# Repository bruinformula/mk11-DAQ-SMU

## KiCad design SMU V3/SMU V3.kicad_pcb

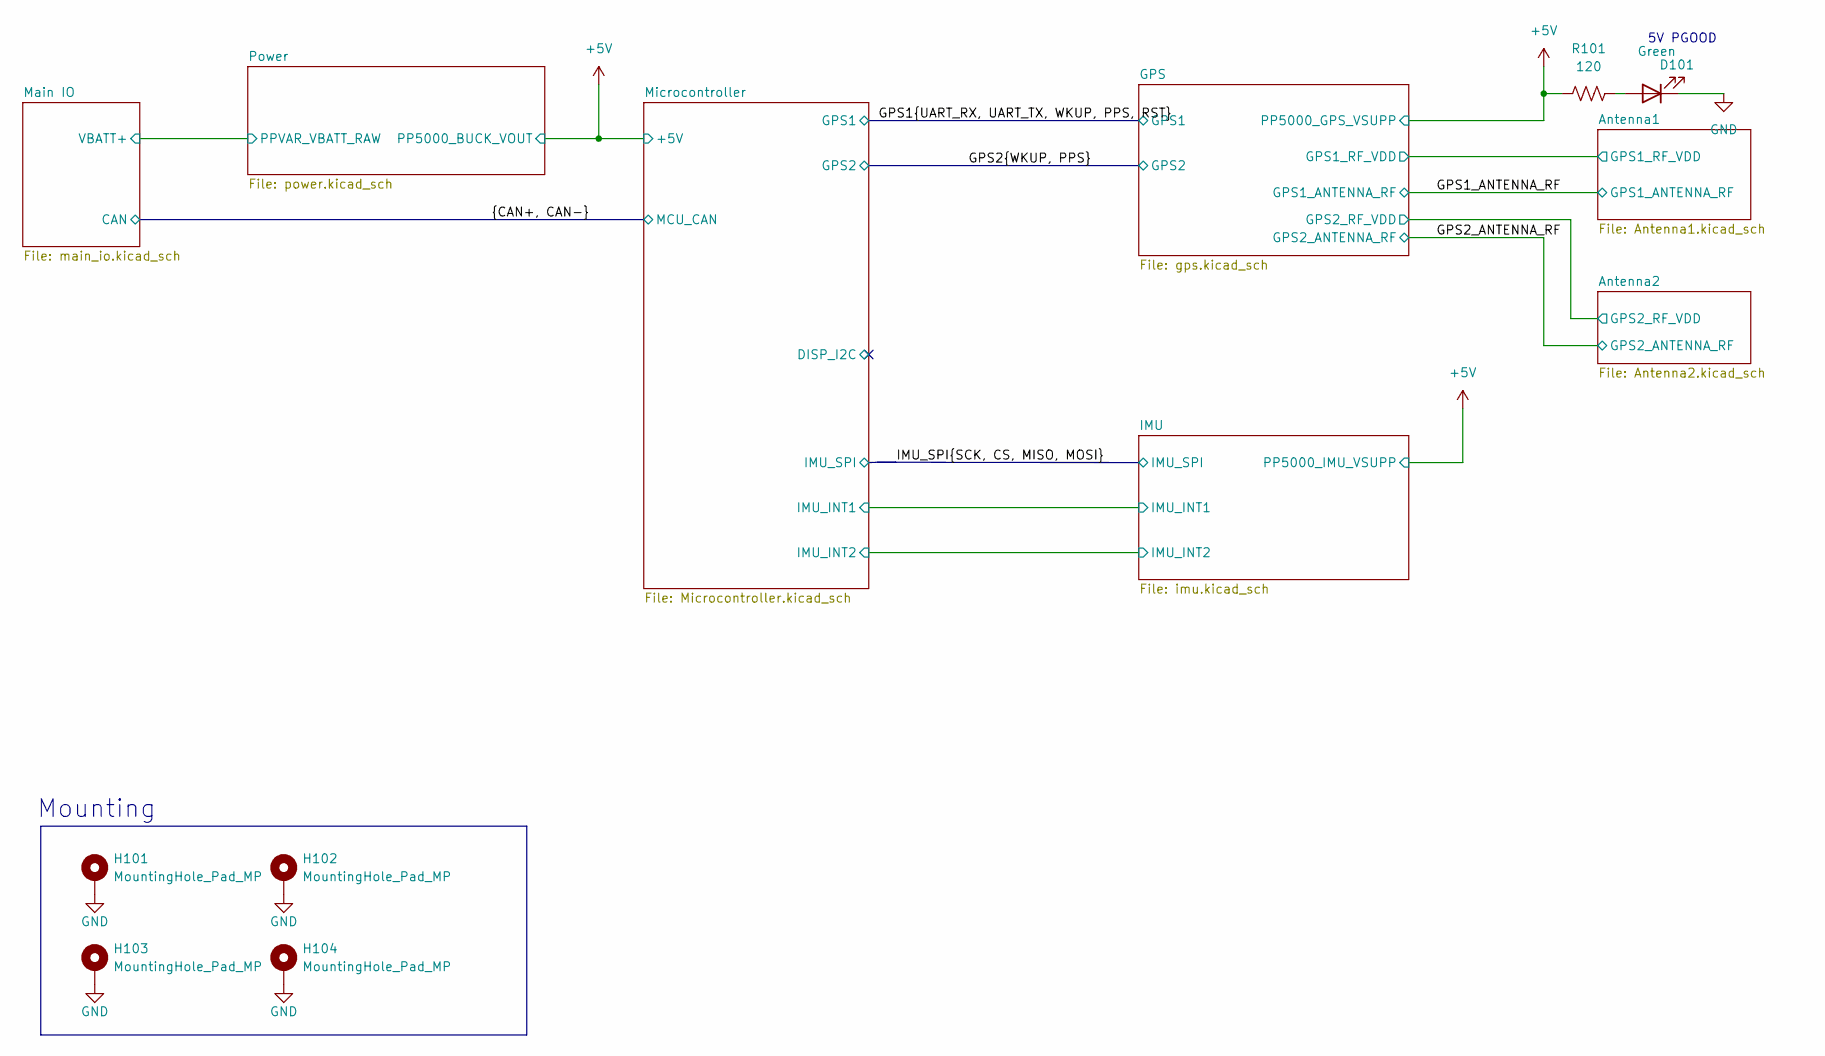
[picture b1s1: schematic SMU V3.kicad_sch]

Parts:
D101: Green; D_0805_2012Metric_Pad1.15x1.40mm_HandSolder; Mouser P/N 755-SMLMN2ECTT86C; Digikey P/N 846-SMLMN2ECTT86CCT-ND
H101, H102, H103, H104: MountingHole_Pad_MP; MountingHole_2.7mm_M2.5_Pad_Via; Mouser P/N N/A; Digikey P/N N/A
R101: 120; R_0603_1608Metric_Pad0.98x0.95mm_HandSolder; Mouser P/N 708-RMCF0603FT120R; Digikey P/N RMCF0603FT120RCT-ND

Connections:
+5V: R101.1; also elsewhere on the board
GND: D101.1 (K), H101.1 (1_1), H102.1 (1_1), H103.1 (1_1), H104.1 (1_1); also elsewhere on the board
unnamed: D101.2 (A), R101.2

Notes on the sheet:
5V PGOOD
Mounting

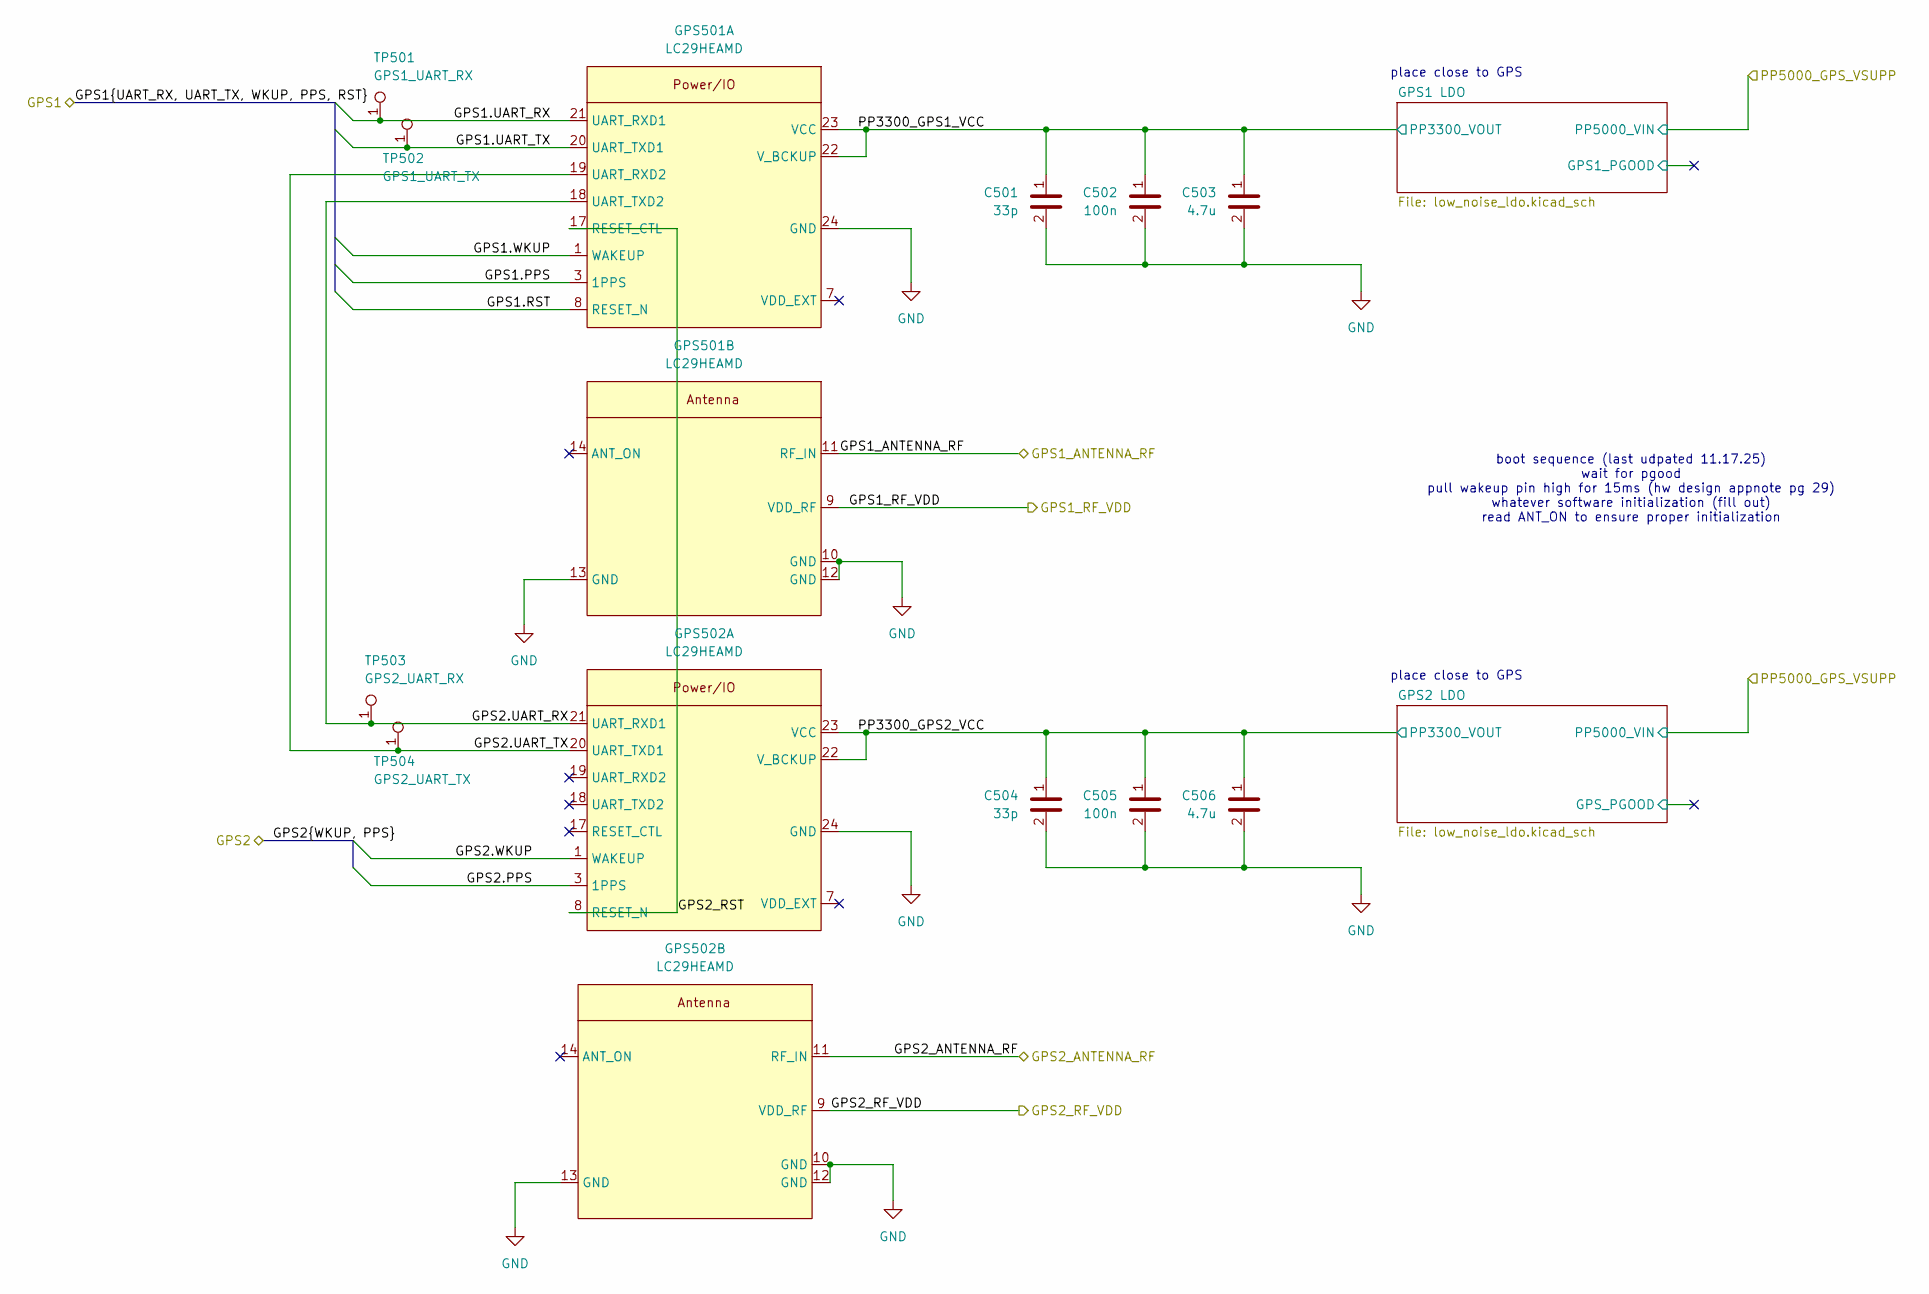
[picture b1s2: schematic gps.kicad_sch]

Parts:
C501, C504: 33p; C_0402_1005Metric_Pad0.74x0.62mm_HandSolder; LCSC P/N C1562
C502, C505: 100n; C_0402_1005Metric_Pad0.74x0.62mm_HandSolder; LCSC P/N C1525
C503, C506: 4.7u; C_0603_1608Metric_Pad1.08x0.95mm_HandSolder; LCSC P/N C19666
GPS501, GPS502: LC29HEAMD; Quectel LC49
TP501: GPS1_UART_RX; TestPoint_Keystone_5019_Miniature; Manufacturer P/N RH-5019; Digikey P/N 36-5019CT-ND
TP502: GPS1_UART_TX; TestPoint_Keystone_5019_Miniature; Manufacturer P/N RH-5019; Digikey P/N 36-5019CT-ND
TP503: GPS2_UART_RX; TestPoint_Keystone_5019_Miniature; Manufacturer P/N RH-5019; Digikey P/N 36-5019CT-ND
TP504: GPS2_UART_TX; TestPoint_Keystone_5019_Miniature; Manufacturer P/N RH-5019; Digikey P/N 36-5019CT-ND

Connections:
/Antenna1/GPS1_RF_VDD: GPS501.9 (VDD_RF); also elsewhere on the board
/Antenna2/GPS2_RF_VDD: GPS502.9 (VDD_RF); also elsewhere on the board
/GPS1.PPS: GPS501.3 (1PPS); also elsewhere on the board
/GPS1.RST: GPS501.8 (RESET_N); also elsewhere on the board
/GPS1.UART_RX: GPS501.21 (UART_RXD1), TP501.1; also elsewhere on the board
/GPS1.UART_TX: GPS501.20 (UART_TXD1), TP502.1; also elsewhere on the board
/GPS1.WKUP: GPS501.1 (WAKEUP); also elsewhere on the board
/GPS1_ANTENNA_RF: GPS501.11 (RF_IN); also elsewhere on the board
/GPS2.PPS: GPS502.3 (1PPS); also elsewhere on the board
/GPS2.WKUP: GPS502.1 (WAKEUP); also elsewhere on the board
/GPS2_ANTENNA_RF: GPS502.11 (RF_IN); also elsewhere on the board
/GPS/GPS2.UART_RX: GPS501.18 (UART_TXD2), GPS502.21 (UART_RXD1), TP503.1
/GPS/GPS2.UART_TX: GPS501.19 (UART_RXD2), GPS502.20 (UART_TXD1), TP504.1
/GPS/GPS2_RST: GPS501.17 (RESET_CTL), GPS502.8 (RESET_N)
/GPS/PP3300_GPS1_VCC: C501.1, C502.1, C503.1, GPS501.22 (V_BCKUP), GPS501.23 (VCC); also elsewhere on the board
/GPS/PP3300_GPS2_VCC: C504.1, C505.1, C506.1, GPS502.22 (V_BCKUP), GPS502.23 (VCC); also elsewhere on the board
GND: C501.2, C502.2, C503.2, C504.2, C505.2, C506.2, GPS501.10 (GND), GPS501.12 (GND), GPS501.13 (GND), GPS501.24 (GND), GPS502.10 (GND), GPS502.12 (GND), GPS502.13 (GND), GPS502.24 (GND); also elsewhere on the board

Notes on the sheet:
boot sequence (last udpated 11.17.25) wait for pgood pull wakeup pin high for 15ms (hw design appnote pg 29) whatever software initialization (fill out) read ANT_ON to ensure proper initialization
place close to GPS

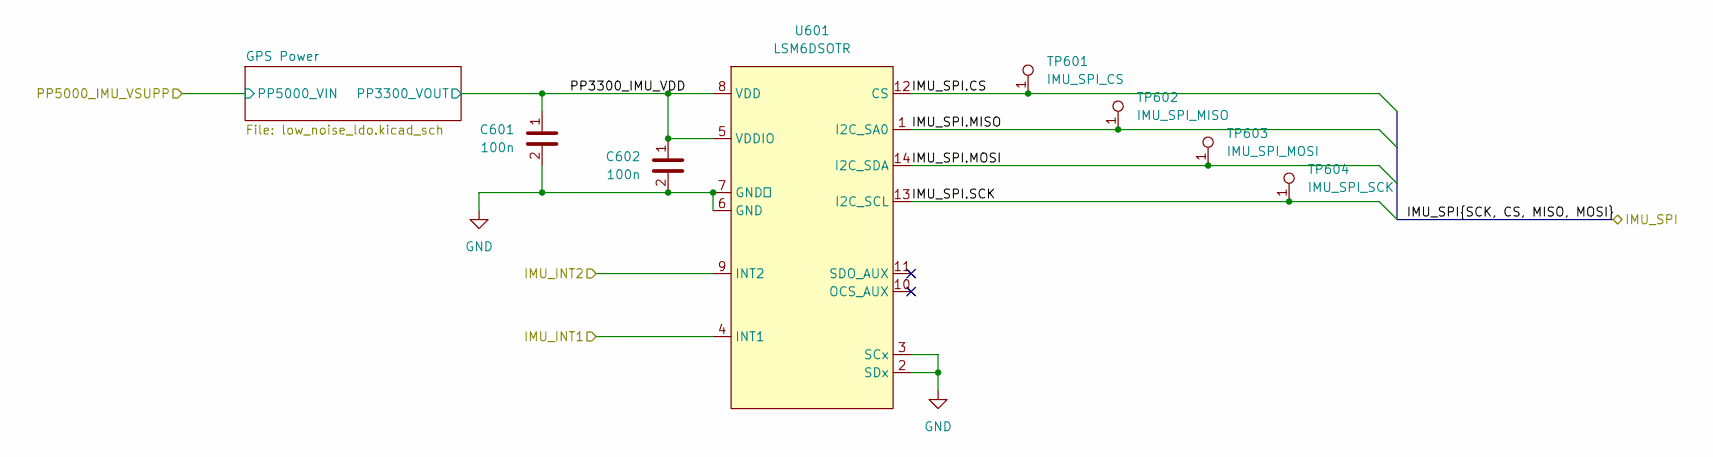
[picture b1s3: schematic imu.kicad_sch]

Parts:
C601, C602: 100n; C_0402_1005Metric_Pad0.74x0.62mm_HandSolder; LCSC P/N C1525
TP601: IMU_SPI_CS; TestPoint_Keystone_5019_Miniature; Manufacturer P/N RH-5019; Digikey P/N 36-5019CT-ND
TP602: IMU_SPI_MISO; TestPoint_Keystone_5019_Miniature; Manufacturer P/N RH-5019; Digikey P/N 36-5019CT-ND
TP603: IMU_SPI_MOSI; TestPoint_Keystone_5019_Miniature; Manufacturer P/N RH-5019; Digikey P/N 36-5019CT-ND
TP604: IMU_SPI_SCK; TestPoint_Keystone_5019_Miniature; Manufacturer P/N RH-5019; Digikey P/N 36-5019CT-ND
U601: LSM6DSOTR; LGA-14_3x2.5mm_P0.5mm_LayoutBorder3x4y; Manufacturer P/N LSM6DSOTR; Digikey P/N 497-18181-2-ND

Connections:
/IMU/IMU_INT1: U601.4 (INT1); also elsewhere on the board
/IMU/IMU_INT2: U601.9 (INT2); also elsewhere on the board
/IMU/PP3300_IMU_VDD: C601.1, C602.1, U601.5 (VDDIO), U601.8 (VDD); also elsewhere on the board
/IMU_SPI.CS: TP601.1, U601.12 (CS); also elsewhere on the board
/IMU_SPI.MISO: TP602.1, U601.1 (I2C_SA0); also elsewhere on the board
/IMU_SPI.MOSI: TP603.1, U601.14 (I2C_SDA); also elsewhere on the board
/IMU_SPI.SCK: TP604.1, U601.13 (I2C_SCL); also elsewhere on the board
GND: C601.2, C602.2, U601.2 (SDx), U601.3 (SCx), U601.6 (GND), U601.7 (GND); also elsewhere on the board

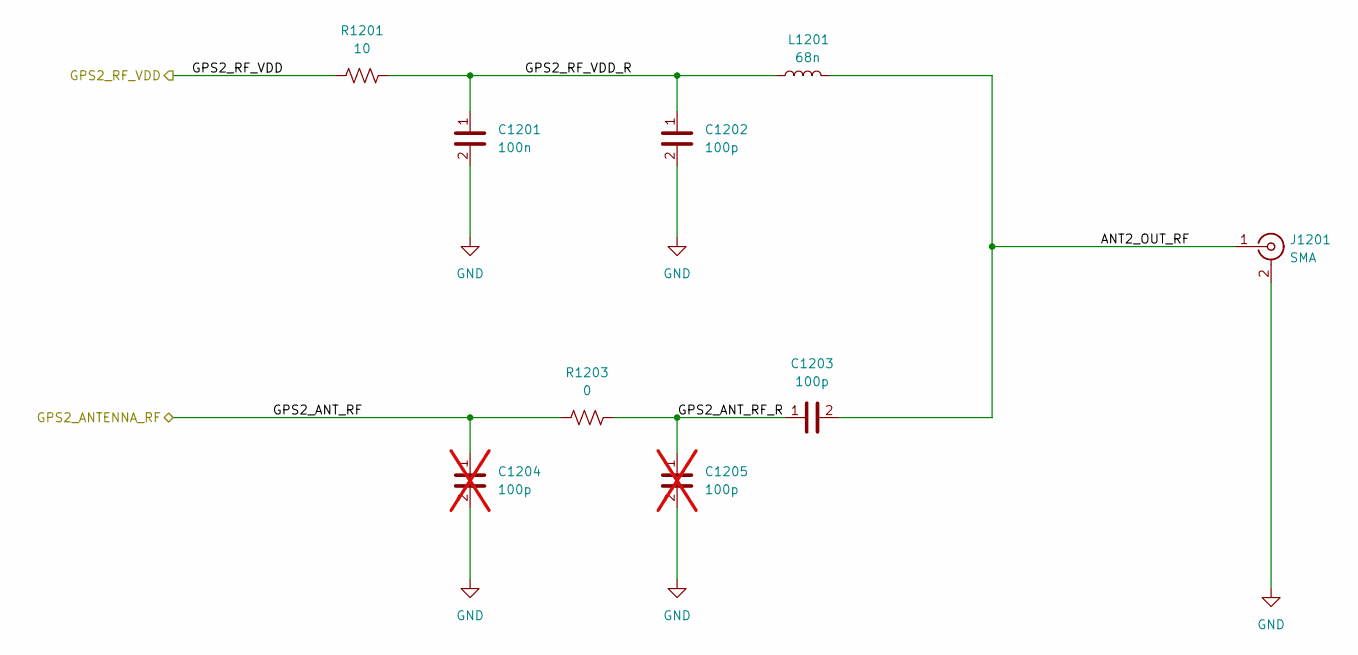
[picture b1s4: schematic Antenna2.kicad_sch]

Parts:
C1201: 100n; C_0402_1005Metric_Pad0.74x0.62mm_HandSolder; Manufacturer P/N CL05B104KB54PNC; LCSC P/N C307331
C1202, C1203: 100p; C_0402_1005Metric_Pad0.74x0.62mm_HandSolder; LCSC P/N C1546
C1204, C1205: 100p; C_0402_1005Metric_Pad0.74x0.62mm_HandSolder; LCSC P/N C1546; not fitted
J1201: SMA; THT SMA; Manufacturer P/N SMA-J-P-H-ST-TH1; Digikey P/N SAM8971-ND
L1201: 68n; L_0402_1005Metric_Pad0.77x0.64mm_HandSolder; Manufacturer P/N LQW15AN68NG0ZD; Digikey P/N 490-17700-2-ND
R1201: 10; R_0402_1005Metric_Pad0.72x0.64mm_HandSolder; Mouser P/N 708-RMCF0402FT10R0; Digikey P/N RMCF0402FT10R0CT-ND
R1203: 0; R_0402_1005Metric_Pad0.72x0.64mm_HandSolder; Mouser P/N 708-RMCF0402ZT0R00; Digikey P/N RMCF0402ZT0R00CT-ND

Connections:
/Antenna2/ANT2_OUT_RF: C1203.2, J1201.1, L1201.1
/Antenna2/GPS2_ANT_RF_R: C1203.1, C1205.1, R1203.2
/Antenna2/GPS2_RF_VDD: R1201.1; also elsewhere on the board
/Antenna2/GPS2_RF_VDD_R: C1201.1, C1202.1, L1201.2, R1201.2
/GPS2_ANTENNA_RF: C1204.1, R1203.1; also elsewhere on the board
GND: C1201.2, C1202.2, C1204.2, C1205.2, J1201.2; also elsewhere on the board

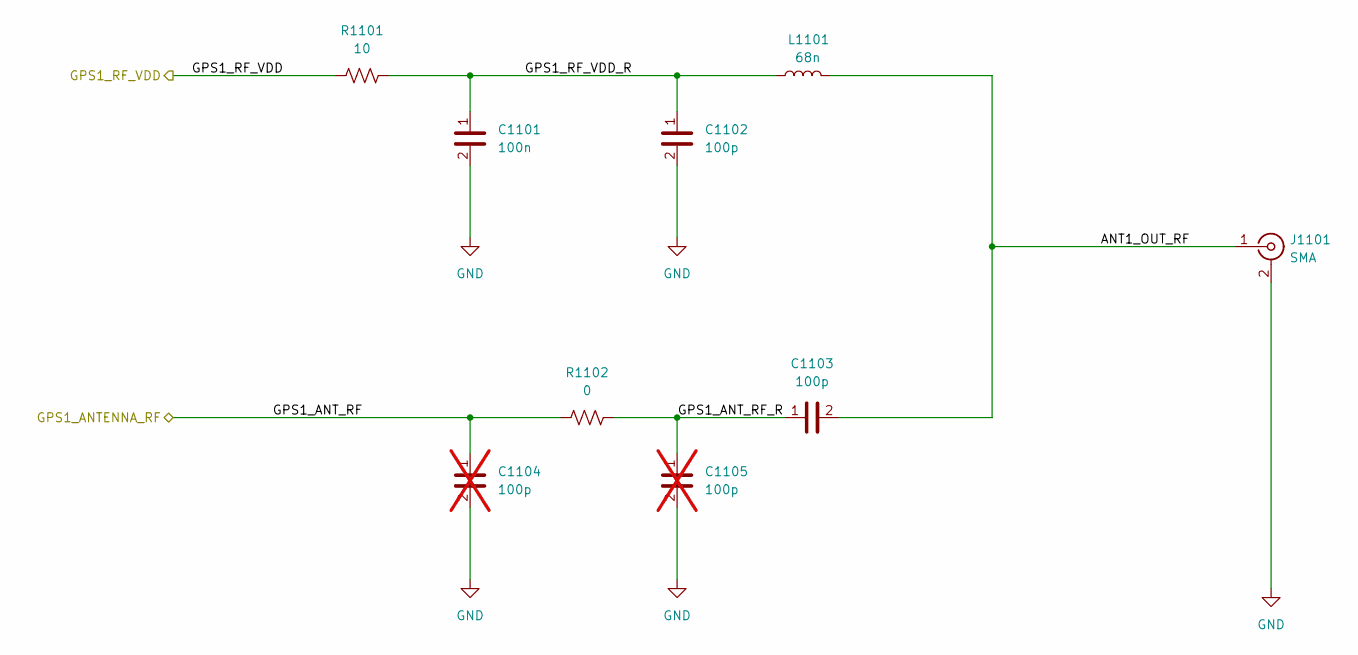
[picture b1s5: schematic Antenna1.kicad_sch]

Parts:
C1101: 100n; C_0402_1005Metric_Pad0.74x0.62mm_HandSolder; Manufacturer P/N CL05B104KB54PNC; LCSC P/N C307331
C1102, C1103: 100p; C_0402_1005Metric_Pad0.74x0.62mm_HandSolder; LCSC P/N C1546
C1104, C1105: 100p; C_0402_1005Metric_Pad0.74x0.62mm_HandSolder; LCSC P/N C1546; not fitted
J1101: SMA; THT SMA; Manufacturer P/N SMA-J-P-H-ST-TH1; Digikey P/N SAM8971-ND
L1101: 68n; L_0402_1005Metric_Pad0.77x0.64mm_HandSolder; Manufacturer P/N LQW15AN68NG0ZD; Digikey P/N 490-17700-2-ND
R1101: 10; R_0402_1005Metric_Pad0.72x0.64mm_HandSolder; Mouser P/N 708-RMCF0402FT10R0; Digikey P/N RMCF0402FT10R0CT-ND
R1102: 0; R_0402_1005Metric_Pad0.72x0.64mm_HandSolder; Mouser P/N 708-RMCF0402ZT0R00; Digikey P/N RMCF0402ZT0R00CT-ND

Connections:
/Antenna1/ANT1_OUT_RF: C1103.2, J1101.1, L1101.1
/Antenna1/GPS1_ANT_RF_R: C1103.1, C1105.1, R1102.2
/Antenna1/GPS1_RF_VDD: R1101.1; also elsewhere on the board
/Antenna1/GPS1_RF_VDD_R: C1101.1, C1102.1, L1101.2, R1101.2
/GPS1_ANTENNA_RF: C1104.1, R1102.1; also elsewhere on the board
GND: C1101.2, C1102.2, C1104.2, C1105.2, J1101.2; also elsewhere on the board

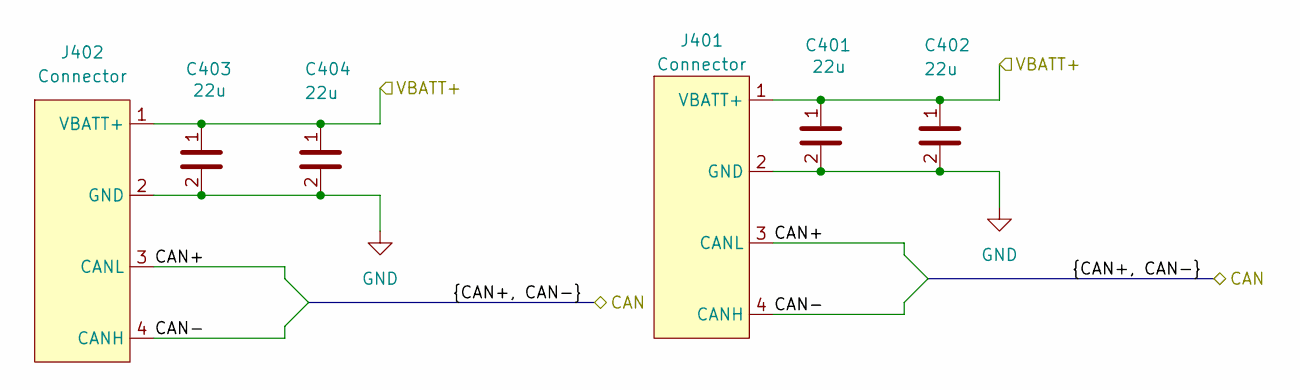
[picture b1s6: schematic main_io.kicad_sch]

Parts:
C401, C402, C403, C404: 22u; C_0805_2012Metric_Pad1.18x1.45mm_HandSolder; Mouser P/N 187-CL21A226MAYNNNE
J401, J402: Connector; Molex_Micro-Fit_3.0_43650-0400_1x04_P3.00mm_Horizontal; Manufacturer P/N 0436500401; Digikey P/N WM1867-ND

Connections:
/CAN+: J401.3 (CANL), J402.3 (CANL); also elsewhere on the board
/CAN-: J401.4 (CANH), J402.4 (CANH); also elsewhere on the board
/Main IO/VBATT+: C401.1, C402.1, C403.1, C404.1, J401.1 (VBATT+), J402.1 (VBATT+); also elsewhere on the board
GND: C401.2, C402.2, C403.2, C404.2, J401.2 (GND), J402.2 (GND); also elsewhere on the board

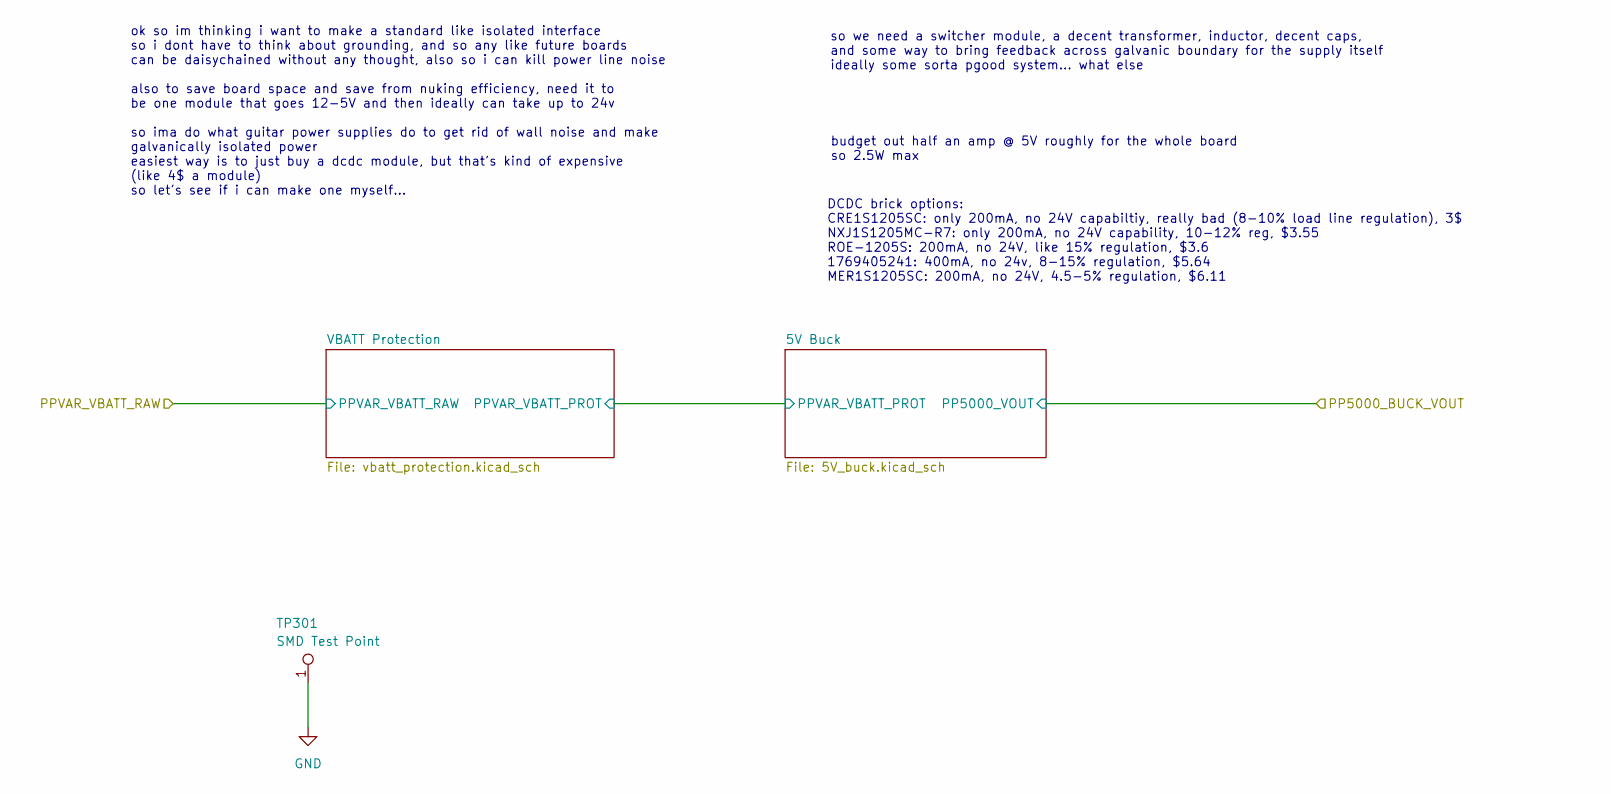
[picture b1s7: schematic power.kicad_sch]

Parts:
TP301: SMD Test Point; TestPoint_Keystone_5019_Miniature; Manufacturer P/N RH-5019; Digikey P/N 36-5019CT-ND

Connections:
GND: TP301.1; also elsewhere on the board

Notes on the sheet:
ok so im thinking i want to make a standard like isolated interface so i dont have to think about grounding, and so any like future boards can be daisychained without any thought, also so i can kill power line noise also to save board space and save from nuking efficiency, need it to be one module 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
so we need a switcher module, a decent transformer, inductor, decent caps, and some way to bring feedback across galvanic boundary for the supply itself ideally some sorta pgood system... what else
DCDC brick options: CRE1S1205SC: only 200mA, no 24V capabiltiy, really bad (8-10% load line regulation), 3$ NXJ1S1205MC-R7: only 200mA, no 24V capability, 10-12% reg, $3.55 ROE-1205S: 200mA, no 24V, like 15% regulation, $3.6 1769405241: 400mA, no 24v, 8-15% regulation, $5.64 MER1S1205SC: 200mA, no 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
budget out half an amp @ 5V roughly for the whole board so 2.5W max

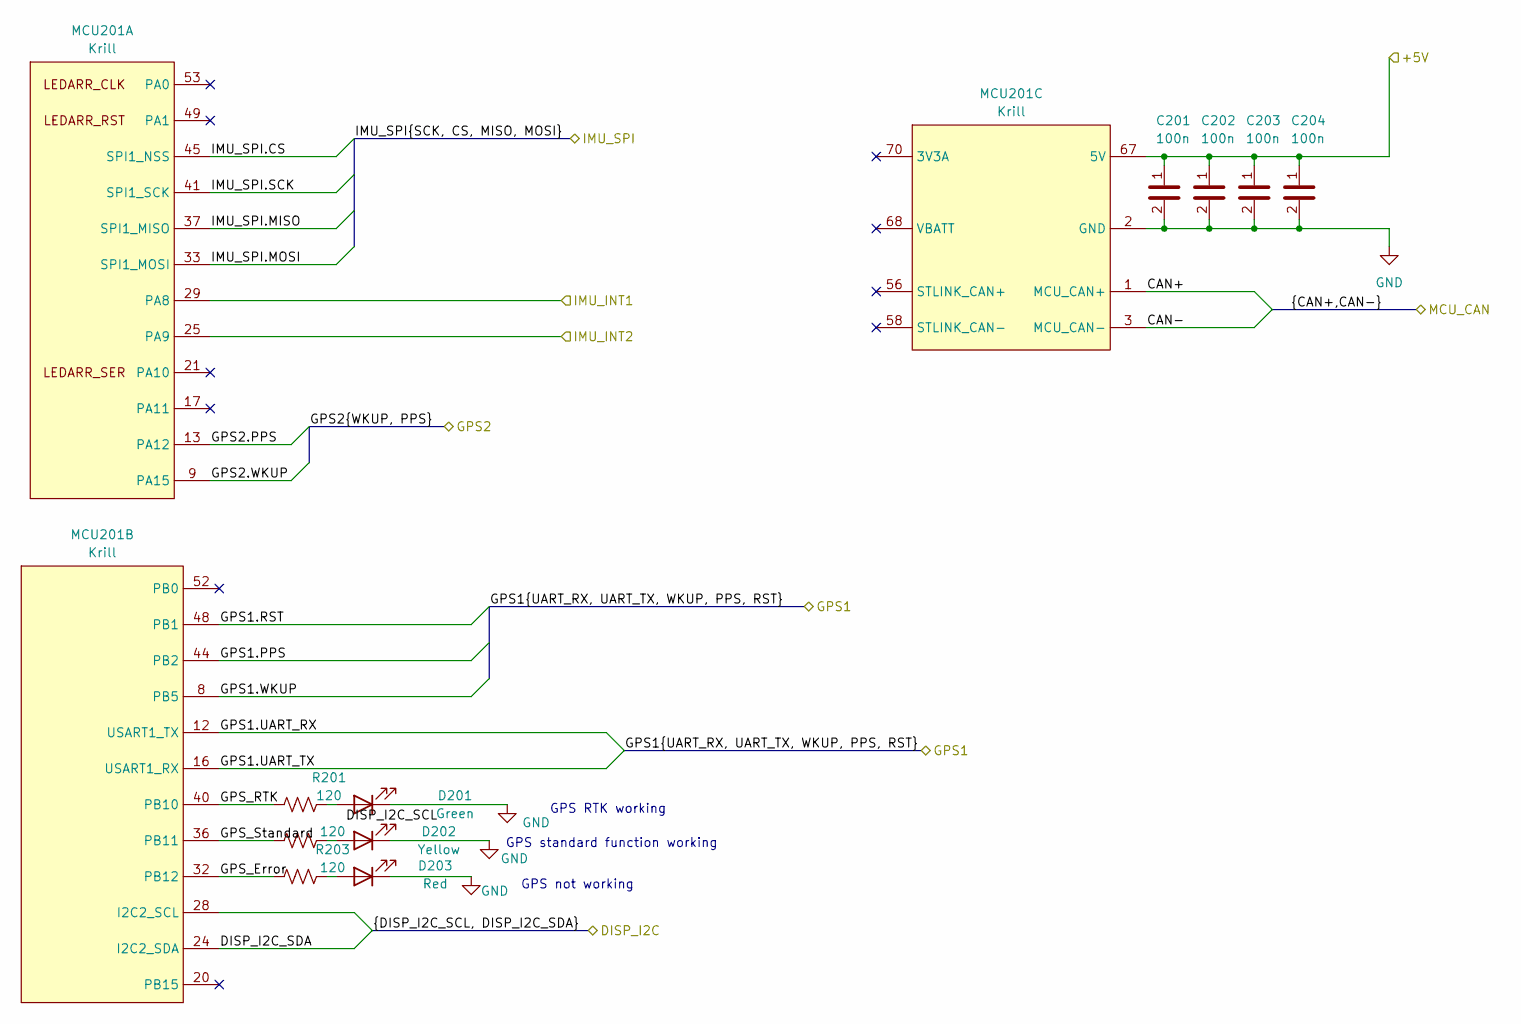
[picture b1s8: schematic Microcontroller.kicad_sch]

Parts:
C201, C202, C203, C204: 100n; C_0402_1005Metric_Pad0.74x0.62mm_HandSolder; LCSC P/N C1525
D201: Green; D_0805_2012Metric_Pad1.15x1.40mm_HandSolder; Mouser P/N 755-SMLMN2ECTT86C; Digikey P/N 846-SMLMN2ECTT86CCT-ND
D202: Yellow; D_0805_2012Metric_Pad1.15x1.40mm_HandSolder; Mouser P/N 645-599-0140-007F; Digikey P/N 350-4356-1-ND
D203: Red; D_0603_1608Metric_Pad1.05x0.95mm_HandSolder; Mouser P/N 720-LRQ976.01; Digikey P/N 475-LRQ976.01-P2R2-1CT-ND
MCU201: Krill; Manufacturer P/N 2E0BC21-S85BM-7H; Digikey P/N 609-MDT850M01501CT-ND
R201, R202, R203: 120; R_0603_1608Metric_Pad0.98x0.95mm_HandSolder; Mouser P/N 708-RMCF0603FT120R; Digikey P/N RMCF0603FT120RCT-ND

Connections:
+5V: C201.1, C202.1, C203.1, C204.1, MCU201.67 (5V), MCU201.69 (5V), MCU201.71 (5V); also elsewhere on the board
/CAN+: MCU201.1 (MCU_CAN+); also elsewhere on the board
/CAN-: MCU201.3 (MCU_CAN-); also elsewhere on the board
/GPS1.PPS: MCU201.44 (PB2); also elsewhere on the board
/GPS1.RST: MCU201.48 (PB1); also elsewhere on the board
/GPS1.UART_RX: MCU201.12 (USART1_TX); also elsewhere on the board
/GPS1.UART_TX: MCU201.16 (USART1_RX); also elsewhere on the board
/GPS1.WKUP: MCU201.8 (PB5); also elsewhere on the board
/GPS2.PPS: MCU201.13 (PA12); also elsewhere on the board
/GPS2.WKUP: MCU201.9 (PA15); also elsewhere on the board
/IMU/IMU_INT1: MCU201.29 (PA8); also elsewhere on the board
/IMU/IMU_INT2: MCU201.25 (PA9); also elsewhere on the board
/IMU_SPI.CS: MCU201.45 (SPI1_NSS); also elsewhere on the board
/IMU_SPI.MISO: MCU201.37 (SPI1_MISO); also elsewhere on the board
/IMU_SPI.MOSI: MCU201.33 (SPI1_MOSI); also elsewhere on the board
/IMU_SPI.SCK: MCU201.41 (SPI1_SCK); also elsewhere on the board
/Microcontroller/DISP_I2C_SDA: MCU201.24 (I2C2_SDA)
/Microcontroller/GPS_Error: MCU201.32 (PB12), R203.1
/Microcontroller/GPS_RTK: MCU201.40 (PB10), R201.1
/Microcontroller/GPS_Standard: MCU201.36 (PB11), R202.1
GND: C201.2, C202.2, C203.2, C204.2, D201.1 (K), D202.1 (K), D203.1 (K), MCU201.2 (GND), MCU201.4 (GND), MCU201.5 (GND), MCU201.6 (GND), MCU201.7 (GND), MCU201.10 (GND), MCU201.11 (GND), MCU201.14 (GND), MCU201.15 (GND), MCU201.18 (GND), MCU201.19 (GND), MCU201.22 (GND), MCU201.23 (GND), MCU201.26 (GND), MCU201.27 (GND), MCU201.30 (GND), MCU201.31 (GND), MCU201.34 (GND), MCU201.35 (GND), MCU201.38 (GND), MCU201.39 (GND), MCU201.42 (GND), MCU201.43 (GND), MCU201.46 (GND), MCU201.47 (GND), MCU201.50 (GND), MCU201.51 (GND), MCU201.54 (GND), MCU201.55 (GND), MCU201.57 (GND), MCU201.73 (GND), MCU201.75 (GND); also elsewhere on the board
unnamed: D201.2 (A), R201.2
unnamed: D202.2 (A), R202.2
unnamed: D203.2 (A), R203.2

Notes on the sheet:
GPS standard function working
GPS not working
GPS RTK working

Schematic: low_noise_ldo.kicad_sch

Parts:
C701, C702: 2.2u; C_0402_1005Metric_Pad0.74x0.62mm_HandSolder; LCSC P/N C12530
D701: Green; D_0805_2012Metric_Pad1.15x1.40mm_HandSolder; Mouser P/N 755-SMLMN2ECTT86C; Digikey P/N 846-SMLMN2ECTT86CCT-ND
R701: 120; R_0603_1608Metric_Pad0.98x0.95mm_HandSolder; Mouser P/N 708-RMCF0603FT120R; Digikey P/N RMCF0603FT120RCT-ND
U701: TPS7A2033PDBVR; SOT-23-5_HandSoldering; Manufacturer P/N TPS7A2033PDBVR; Digikey P/N 296-TPS7A2033PDBVRCT-ND

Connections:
+5V: C701.1, U701.1 (VIN), U701.3 (EN); also elsewhere on the board
/GPS/PP3300_GPS1_VCC: C702.1, R701.1, U701.5 (VOUT); also elsewhere on the board
GND: C701.2, C702.2, D701.1 (K), U701.2 (GND); also elsewhere on the board
unnamed: D701.2 (A), R701.2

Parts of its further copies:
C801, C802, C901, C902: 2.2u; C_0402_1005Metric_Pad0.74x0.62mm_HandSolder; LCSC P/N C12530
D801, D901: Green; D_0805_2012Metric_Pad1.15x1.40mm_HandSolder; Mouser P/N 755-SMLMN2ECTT86C; Digikey P/N 846-SMLMN2ECTT86CCT-ND
R801, R901: 120; R_0603_1608Metric_Pad0.98x0.95mm_HandSolder; Mouser P/N 708-RMCF0603FT120R; Digikey P/N RMCF0603FT120RCT-ND
U801, U901: TPS7A2033PDBVR; SOT-23-5_HandSoldering; Manufacturer P/N TPS7A2033PDBVR; Digikey P/N 296-TPS7A2033PDBVRCT-ND

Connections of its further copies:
+5V: C801.1, C901.1, U801.1 (VIN), U801.3 (EN), U901.1 (VIN), U901.3 (EN); also elsewhere on the board
/GPS/PP3300_GPS2_VCC: C802.1, R801.1, U801.5 (VOUT); also elsewhere on the board
/IMU/PP3300_IMU_VDD: C902.1, R901.1, U901.5 (VOUT); also elsewhere on the board
GND: C801.2, C802.2, C901.2, C902.2, D801.1 (K), D901.1 (K), U801.2 (GND), U901.2 (GND); also elsewhere on the board
unnamed: D801.2 (A), R801.2
unnamed: D901.2 (A), R901.2

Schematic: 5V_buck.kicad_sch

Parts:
C1001: 1.8p; C_0805_2012Metric_Pad1.18x1.45mm_HandSolder; Mouser P/N 581-600F1R8BT; Digikey P/N 1284-1034-1-ND
C1002: 10n; C_0603_1608Metric_Pad1.08x0.95mm_HandSolder; Mouser P/N 77-VJ0603Y103KXAAC; Digikey P/N 720-1376-1-ND
C1003, C1004: 22u; C_0603_1608Metric_Pad1.08x0.95mm_HandSolder; LCSC P/N C59461
C1005, C1006, C1007, C1008, C1009: 100u; C_1206_3216Metric_Pad1.33x1.80mm_HandSolder; LCSC P/N C15008
D1001: 550m; D_SMA_Handsoldering; Mouser P/N 750-SS54-HF; LCSC P/N C22452
R1001: 180k; R_0805_2012Metric_Pad1.20x1.40mm_HandSolder; Mouser P/N 708-RMCF0805FT180K; Digikey P/N RMCF0805FT180KCT-ND
R1002: 10k; R_0402_1005Metric_Pad0.72x0.64mm_HandSolder; Mouser P/N 708-RMCF0402FT10K0; Digikey P/N RMCF0402FT10K0CT-ND
R1003: 3.3k; R_0402_1005Metric_Pad0.72x0.64mm_HandSolder; Mouser P/N 708-RMCF0402FT3K30; Digikey P/N RMCF0402FT3K30CT-ND
U1001: ETQ-P3M150KVN; BWVS005050404R7M00; Manufacturer P/N ETQ-P3M150KVN; Digikey P/N P19763CT-ND
U1002: TPS5430DDAR; TI_SO-PowerPAD-8; Mouser P/N 595-TPS5430DDAR; Digikey P/N 296-26988-1-ND

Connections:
+5V: C1005.1, C1006.1, C1007.1, C1008.1, C1009.1, R1002.2, U1001.2; also elsewhere on the board
/Power/5V Buck/BUCK_VSENSE: R1002.1, R1003.2, U1002.4 (VSENSE)
/Power/5V Buck/PPVAR_VBATT_PROT: C1001.1, C1003.1, C1004.1, U1002.7 (VIN); also elsewhere on the board
/Power/5V Buck/Rsnub: C1001.2, R1001.1
/Power/5V Buck/SWITCH_NODE: C1002.2, D1001.1 (K), R1001.2, U1001.1, U1002.8 (PH)
GND: C1003.2, C1004.2, C1005.2, C1006.2, C1007.2, C1008.2, C1009.2, D1001.2 (A), R1003.1, U1002.6 (GND), U1002.9 (GNDPAD); also elsewhere on the board
unnamed: C1002.1, U1002.1 (BOOT)

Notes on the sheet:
RC Snubber design: goal is to get Q=1 (critically damped) for the LC tank between U1002 and U1001 internal FET so, we take R=2*pi*F_sw*L (from a rlc shit i forgot) sim says switching freq is 2GHz R=2*3.14*2*10^9*15*10^-6 = 188495 chat what does this mean! now size C based off power..; P = C * Vcc^2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

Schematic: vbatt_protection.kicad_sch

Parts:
D1201: Green; D_0805_2012Metric_Pad1.15x1.40mm_HandSolder; Mouser P/N 755-SMLMN2ECTT86C; Digikey P/N 846-SMLMN2ECTT86CCT-ND
F1201: 500mA; Fuse_1812_4532Metric; Manufacturer P/N 0ZCG0050AF2C; Digikey P/N 5923-0ZCG0050AF2CCT-ND
Q1201: SI2301CDS-T1-GE3; SOT-23-3; Mouser P/N 781-SI2301CDS-T1-GE3; LCSC P/N C10487
R1202: 1.8k; R_0603_1608Metric_Pad0.98x0.95mm_HandSolder; Mouser P/N 708-RMCF0603FT1K80; Digikey P/N RMCF0603FT1K80CT-ND
TVS1201: 16Vrwm; D_SMA-SMB_Universal_Handsoldering; Manufacturer P/N SMBJ16A; Digikey P/N SMBJ16ABCT-ND

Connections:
/Main IO/VBATT+: Q1201.2 (S); also elsewhere on the board
/Power/5V Buck/PPVAR_VBATT_PROT: F1201.2, R1202.1; also elsewhere on the board
GND: D1201.1 (K), Q1201.1 (G), TVS1201.2; also elsewhere on the board
unnamed: D1201.2 (A), R1202.2
unnamed: F1201.1, Q1201.3 (D), TVS1201.1

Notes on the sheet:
board-wide PGOOD LED

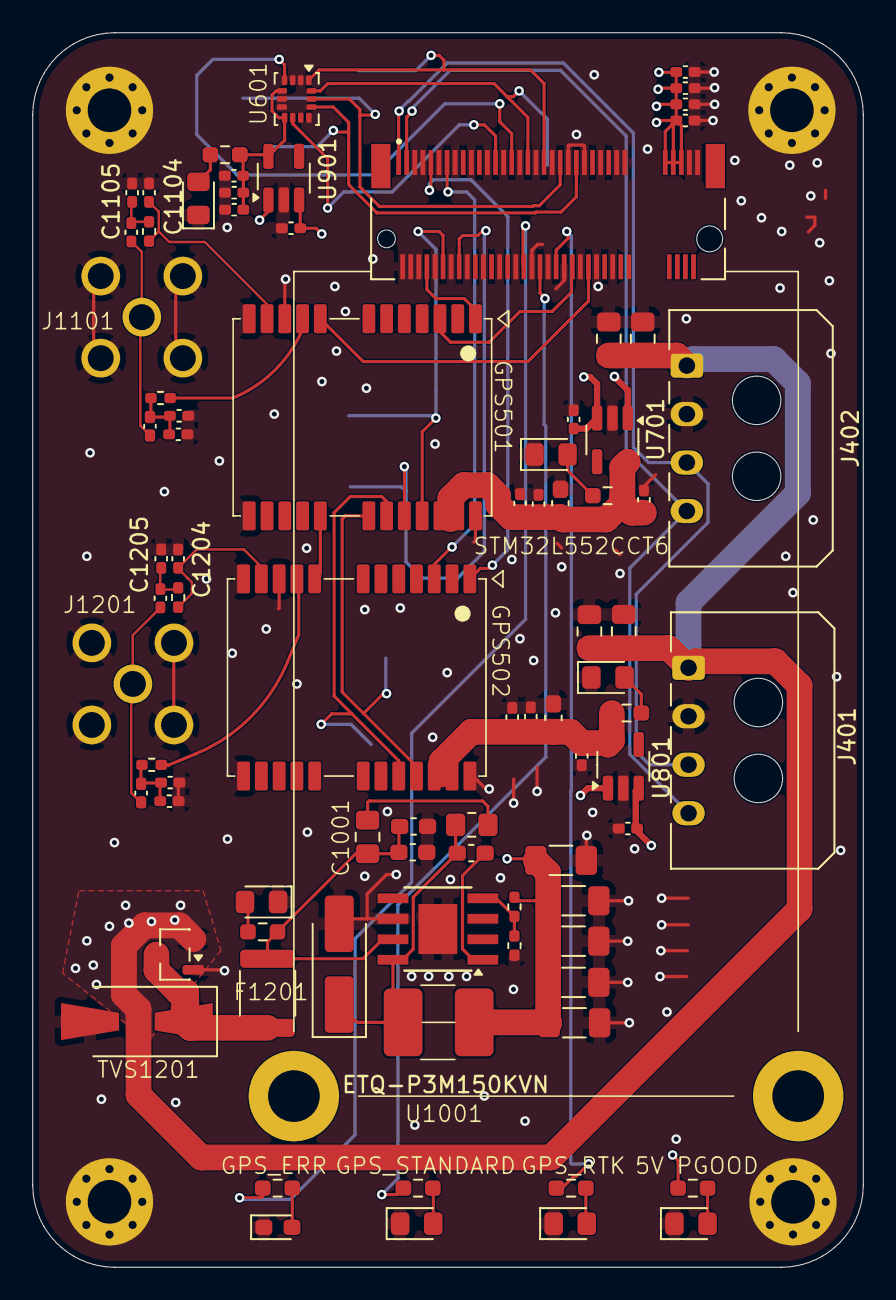
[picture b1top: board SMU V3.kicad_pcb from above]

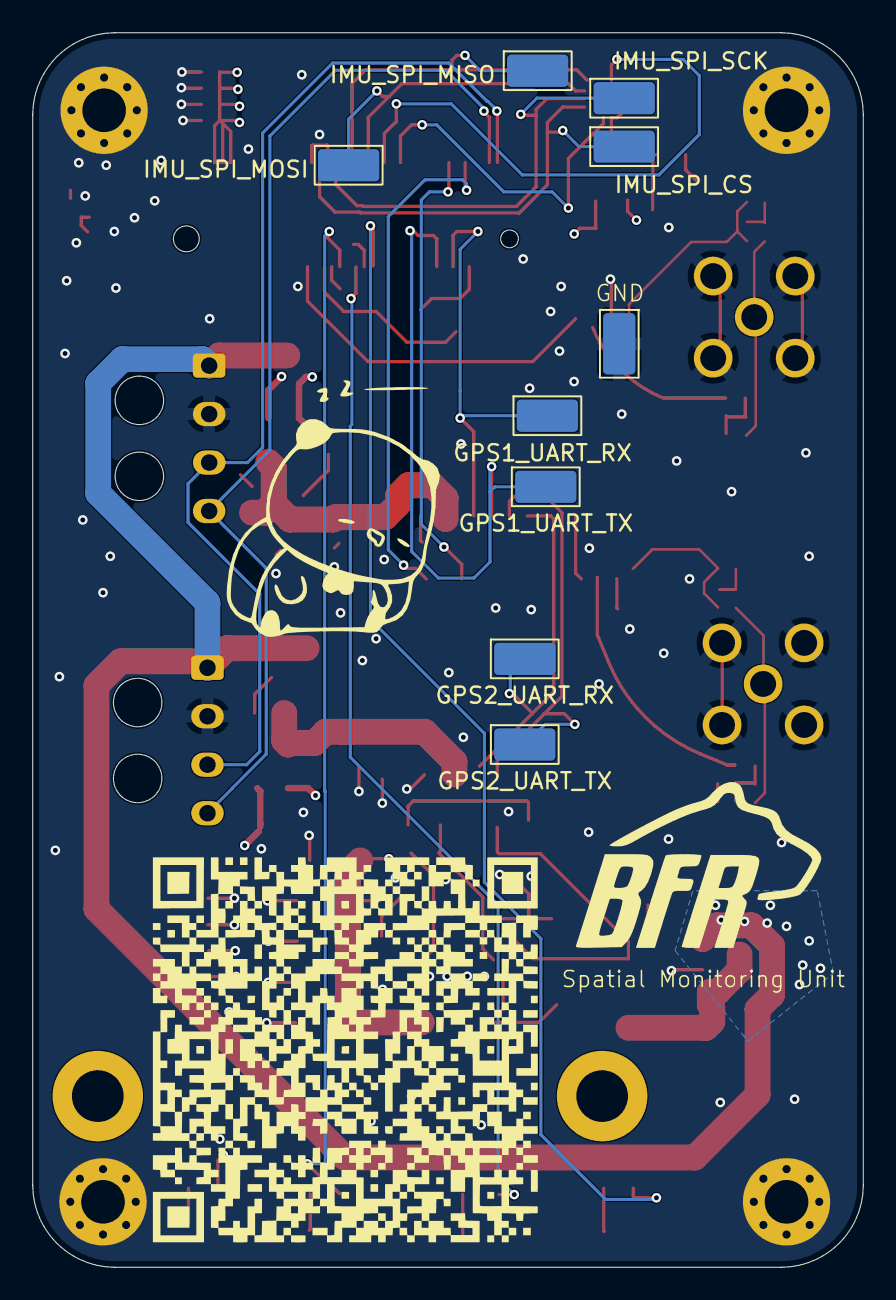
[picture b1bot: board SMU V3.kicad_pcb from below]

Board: 4 copper layers, 51.4 x 76.4 mm, 96 parts (9 on the bottom side), 51 nets.

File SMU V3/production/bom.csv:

Designator,Footprint,Quantity,Value,LCSC Part #
C1001,0805,1,1.8p,C376870
C1002,0603,1,10n,C57112
"C1003, C1004",0603,2,22u,C59461
"C1005, C1006, C1007, C1008, C1009",1206,5,100u,C15008
"C1101, C1201",0402,2,100n,C307331
"C1102, C1103, C1104, C1105, C1202, C1203, C1204, C1205",0402,8,100p,C1546
"C201, C202, C203, C204, C502, C505, C601, C602",0402,8,100n,C1525
"C401, C402, C403, C404",0805,4,22u,C45783
"C501, C504",0402,2,33p,C1562
"C503, C506",0603,2,4.7u,C19666
"C701, C702, C801, C802, C901, C902",0402,6,2.2u,C12530
D1001,D_SMA_Handsoldering,1,550m,C22452
"D101, D1201, D201, D701, D801, D901",0805,6,Green,C2297
D202,0805,1,Yellow,C2296
D203,0603,1,Red,C2286
F1201,1812,1,500mA,C3762102
"GPS501, GPS502",Quectel LC49,2,LC29HEAMD,
"J1101, J1201",THT SMA,2,SMA,C5199904
"J401, J402",Molex_Micro-Fit_3.0_43650-0400_1x04_P3.00mm_Horizontal,2,Connector,
"L1101, L1201",0402,2,68n,C2044127
MCU201,Krill,1,Krill,C410529
Q1201,SOT-23-3,1,SI2301CDS-T1-GE3,C10487
R1001,0805,1,180k,C17501
R1002,0402,1,10k,C25744
R1003,0402,1,3.3k,C25890
"R101, R201, R202, R203, R701, R801, R901",0603,7,120,C22787
"R1101, R1201",0402,2,10,C25077
"R1102, R1203",0402,2,0,C17168
R1202,0603,1,1.8k,C4177
TP301,TestPoint_Keystone_5019_Miniature,1,SMD Test Point,C5199800
TP501,TestPoint_Keystone_5019_Miniature,1,GPS1_UART_RX,C5199800
TP502,TestPoint_Keystone_5019_Miniature,1,GPS1_UART_TX,C5199800
TP503,TestPoint_Keystone_5019_Miniature,1,GPS2_UART_RX,C5199800
TP504,TestPoint_Keystone_5019_Miniature,1,GPS2_UART_TX,C5199800
TP601,TestPoint_Keystone_5019_Miniature,1,IMU_SPI_CS,C5199800
TP602,TestPoint_Keystone_5019_Miniature,1,IMU_SPI_MISO,C5199800
TP603,TestPoint_Keystone_5019_Miniature,1,IMU_SPI_MOSI,C5199800
TP604,TestPoint_Keystone_5019_Miniature,1,IMU_SPI_SCK,C5199800
TVS1201,D_SMA-SMB_Universal_Handsoldering,1,16Vrwm,C19077571
U1001,BWVS005050404R7M00,1,ETQ-P3M150KVN,C3223274
U1002,TI_SO-PowerPAD-8,1,TPS5430DDAR,C9864
U601,LGA-14_3x2.5mm_P0.5mm_LayoutBorder3x4y,1,LSM6DSOTR,C481766
"U701, U801, U901",SOT-23-5_HandSoldering,3,TPS7A2033PDBVR,TPS7A2033PDBVR
